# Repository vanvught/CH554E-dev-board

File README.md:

# CH554E development board

Please let me know by means of an issue when you have open source software using this board and I will add it here. Thanks.

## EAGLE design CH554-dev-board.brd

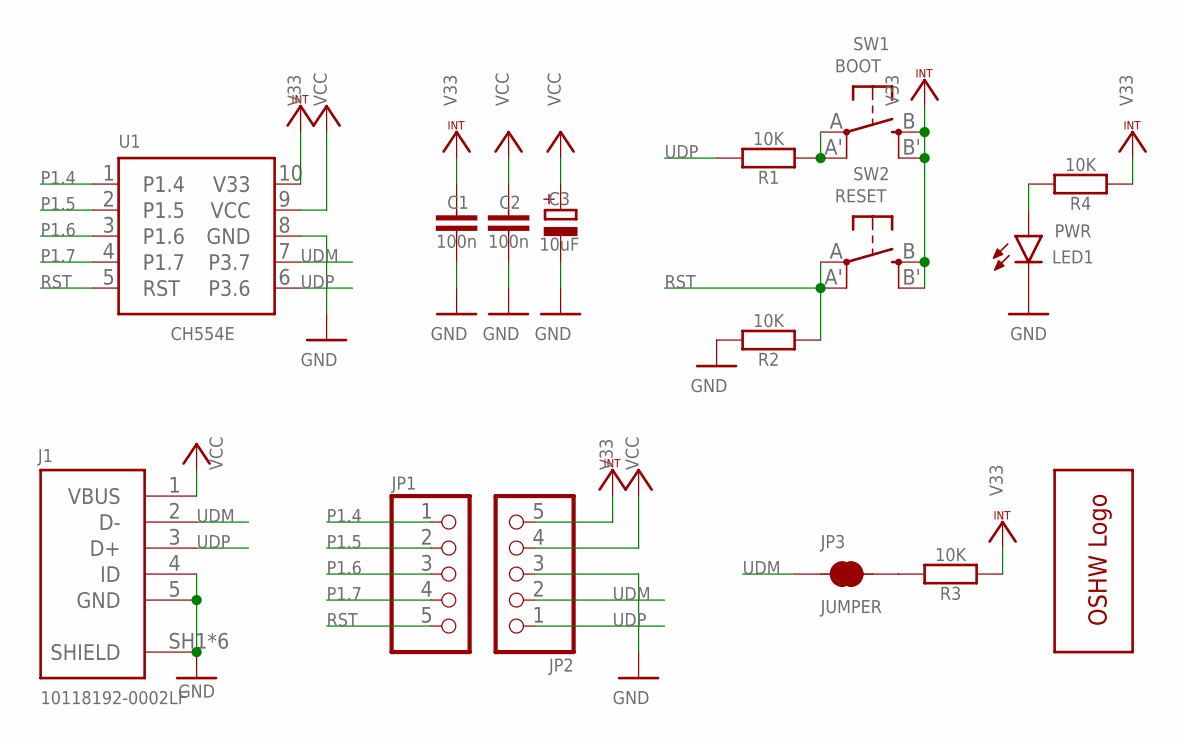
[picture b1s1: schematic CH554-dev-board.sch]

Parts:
C1, C2: 100n; C0603; JLCPCB C14663
C3: 10uF; A/3216-18R; JLCPCB C7171
GOLD_ORB_SM1: OSHWLOGOLOGO5MM; OSHW_5MM
J1: 10118192-0002LF; JLCPCB C2972784
JP1, JP2: PINHD-1X5; 1X05
JP3: JUMPER; SMT-JUMPER_2_NC_TRACE_NO-SILK
LED1: PWR; CHIP-LED0603; JLCPCB C72043
R1, R2, R3, R4: 10K; R0603; JLCPCB C25804
SW1: BOOT; EVQ-Q2; JLCPCB C221880
SW2: RESET; EVQ-Q2; JLCPCB C221880
U1: CH554E; MSOP10

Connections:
GND: C1.2, C2.2, C3.-, J1.4 (ID), J1.5 (GND), J1.SH1 (SHIELD), J1.SH2 (SHIELD), J1.SH3 (SHIELD), J1.SH4 (SHIELD), J1.SH5 (SHIELD), J1.SH6 (SHIELD), JP2.3, LED1.C, R2.2, U1.8 (GND)
unnamed: R1.1, SW1.A, SW1.A' (P1)
unnamed: LED1.A, R4.2
unnamed: JP3.2, R3.2
P1.4: JP1.1, U1.1 (P1.4)
P1.5: JP1.2, U1.2 (P1.5)
P1.6: JP1.3, U1.3 (P1.6)
P1.7: JP1.4, U1.4 (P1.7)
RST: JP1.5, R2.1, SW2.A, SW2.A' (P1), U1.5 (RST)
UDM: J1.2 (D-), JP2.2, JP3.1, U1.7 (P3.7)
UDP: J1.3 (D+), JP2.1, R1.2, U1.6 (P3.6)
V33: C1.1, JP2.5, R3.1, R4.1, SW1.B (S), SW1.B' (S1), SW2.B (S), SW2.B' (S1), U1.10 (V33)
VCC: C2.1, C3.+, J1.1 (VBUS), JP2.4, U1.9 (VCC)

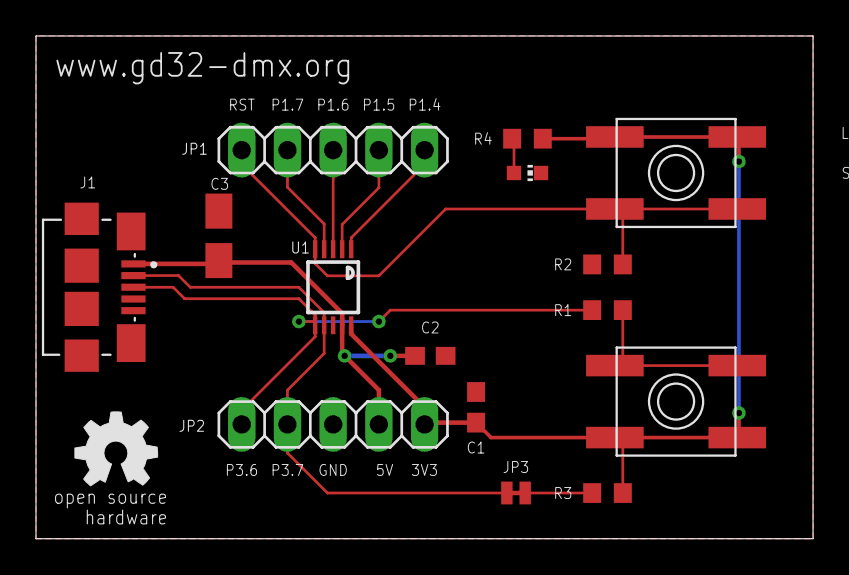
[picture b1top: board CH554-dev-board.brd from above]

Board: 2 copper layers, 43.2 x 27.9 mm, 16 parts (0 on the bottom side), 13 nets.

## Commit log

2024-10-04 Reduced png size
2024-10-04 Fixed typo's
2024-10-04 Fixed size

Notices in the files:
parts and their libraries:
SparkFun-Jumpers: Licensing: Creative Commons ShareAlike 4.0 International - https://creativecommons.org/licenses/by-sa/4.0
